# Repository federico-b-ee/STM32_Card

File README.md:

# STM32_Card
This is the first PCB I have designed and professionally assembled. I used KiCAD v7 and JLC PCBs' services.

# Schematic and 3D-view 

# Picture and Demo

*Note: The gif above was made using the Adafruit's Demo:

- [Library](https://github.com/adafruit/Adafruit_IS31FL3731)
- [Overview](https://learn.adafruit.com/i31fl3731-16x9-charliplexed-pwm-led-driver/overview)

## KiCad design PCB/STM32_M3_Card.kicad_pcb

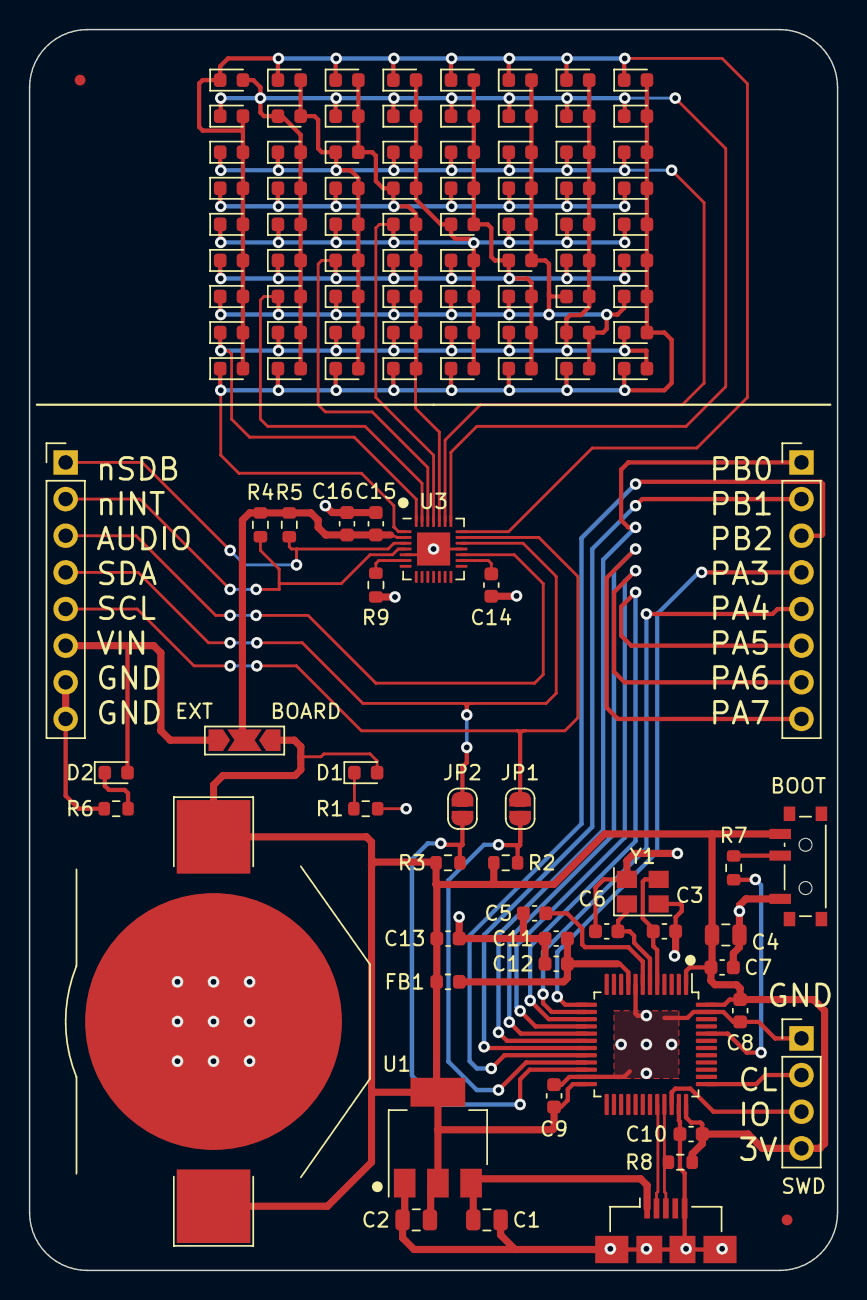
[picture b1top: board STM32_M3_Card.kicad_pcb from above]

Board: 2 copper layers, 56.0 x 86.0 mm, 115 parts (0 on the bottom side), 43 nets.

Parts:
BT1: Coin_Cell; BatteryHolder_Keystone_3002_1x2032
C1, C2: 22u; C_0805_2012Metric
C3, C6: 10p; C_0603_1608Metric
C4: 10u; C_0805_2012Metric
C5, C7, C8, C9, C10, C14, C15: 100n; C_0603_1608Metric
C11: 10n; C_0603_1608Metric
C12, C13, C16: 1u; C_0603_1608Metric
D1, D2, D3, D4, D5, D6, D7, D8, D9, D10, D11, D12, D13, D14, D15, D16, D17, D18, D19, D20, D21, D22, D23, D24, D25, D26, D27, D28, D29, D30, D31, D32, D33, D34, D35, D36, D37, D38, D39, D40, D41, D42, D43, D44, D45, D46, D47, D48, D49, D50, D51, D52, D53, D54, D55, D56, D57, D58, D59, D60, D61, D62, D63, D64, D65, D66, D67, D68, D69, D70, D71, D72, D73, D74: LED (RED); LED_0603_1608Metric
FB1: 120R; L_0603_1608Metric
FID1, FID2: Fiducial; Fiducial_0.75mm_Mask1.5mm
J1, J3: Conn_01x08_Pin; PinHeader_1x08_P2.54mm_Vertical
J2: USB_B_Micro; USB_Micro-B_Amphenol_10104110_Horizontal
J4: Conn_01x04_Pin; PinHeader_1x04_P2.54mm_Vertical
JP1, JP2: SolderJumper_2_Open; SolderJumper-2_P1.3mm_Open_RoundedPad1.0x1.5mm
JP3: SolderJumper_3_Open; SolderJumper-3_P2.0mm_Open_TrianglePad1.0x1.5mm_NumberLabels
R1, R6: 680R; R_0603_1608Metric
R2, R3, R8: 1k5; R_0603_1608Metric
R4, R5, R7, R9: 18k; R_0603_1608Metric
SW1: SW_SPDT; SW_SPDT_PCM12
U1: AMS1117-3.3; SOT-223-3_TabPin2
U2: STM32F103C8T6; LQFP-48_7x7mm_P0.5mm
U3: IS31FL3731-QF; QFN-28-1EP_4x4mm_P0.4mm_EP2.3x2.3mm
Y1: 16MHz 10pF; Crystal_SMD_3225-4Pin_3.2x2.5mm

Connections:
+3.3VA: C11.1, C12.1, FB1.1, U2.9 (VDDA)
+3.3VP: C15.1, C16.1, JP3.2 (C), R4.1, R5.1, U3.2 (VCC)
+3V3: BT1.1 (+), C2.1, C4.1, C7.1, C8.1, C9.1, C10.1, C13.1, D1.2 (A), FB1.2, J4.4, JP3.1 (A), R2.1, R3.1, R8.1, SW1.3 (C), U1.2 (VO), U2.1 (VBAT), U2.24 (VDD), U2.36 (VDD), U2.48 (VDD)
/AMS_LEDK: D1.1 (K), R1.2
/AUD_IS31: J3.3, U3.17 (IN)
/D+: J2.3 (D+), R8.2, U2.33 (PA12)
/D-: J2.2 (D-), U2.32 (PA11)
/EXT_LEDK: D2.1 (K), R6.2
/IS31FL3731/CA1: D3.1 (K), D4.2 (A), D5.2 (A), D6.2 (A), D7.2 (A), D8.2 (A), D9.2 (A), D10.2 (A), D11.2 (A), D12.1 (K), D21.1 (K), D30.1 (K), D39.1 (K), D48.1 (K), D57.1 (K), D66.1 (K), U3.21 (CA1)
/IS31FL3731/CA2: D3.2 (A), D4.1 (K), D13.1 (K), D14.2 (A), D15.2 (A), D16.2 (A), D17.2 (A), D18.2 (A), D19.2 (A), D20.2 (A), D22.1 (K), D31.1 (K), D40.1 (K), D49.1 (K), D58.1 (K), D67.1 (K), U3.22 (CA2)
/IS31FL3731/CA3: D5.1 (K), D12.2 (A), D13.2 (A), D14.1 (K), D23.1 (K), D24.2 (A), D25.2 (A), D26.2 (A), D27.2 (A), D28.2 (A), D29.2 (A), D32.1 (K), D41.1 (K), D50.1 (K), D59.1 (K), D68.1 (K), U3.23 (CA3)
/IS31FL3731/CA4: D6.1 (K), D15.1 (K), D21.2 (A), D22.2 (A), D23.2 (A), D24.1 (K), D33.1 (K), D34.2 (A), D35.2 (A), D36.2 (A), D37.2 (A), D38.2 (A), D42.1 (K), D51.1 (K), D60.1 (K), D69.1 (K), U3.24 (CA4)
/IS31FL3731/CA5: D7.1 (K), D16.1 (K), D25.1 (K), D30.2 (A), D31.2 (A), D32.2 (A), D33.2 (A), D34.1 (K), D43.1 (K), D44.2 (A), D45.2 (A), D46.2 (A), D47.2 (A), D52.1 (K), D61.1 (K), D70.1 (K), U3.25 (CA5)
/IS31FL3731/CA6: D8.1 (K), D17.1 (K), D26.1 (K), D35.1 (K), D39.2 (A), D40.2 (A), D41.2 (A), D42.2 (A), D43.2 (A), D44.1 (K), D53.1 (K), D54.2 (A), D55.2 (A), D56.2 (A), D62.1 (K), D71.1 (K), U3.26 (CA6)
/IS31FL3731/CA7: D9.1 (K), D18.1 (K), D27.1 (K), D36.1 (K), D45.1 (K), D48.2 (A), D49.2 (A), D50.2 (A), D51.2 (A), D52.2 (A), D53.2 (A), D54.1 (K), D63.1 (K), D64.2 (A), D65.2 (A), D72.1 (K), U3.27 (CA7)
/IS31FL3731/CA8: D10.1 (K), D19.1 (K), D28.1 (K), D37.1 (K), D46.1 (K), D55.1 (K), D57.2 (A), D58.2 (A), D59.2 (A), D60.2 (A), D61.2 (A), D62.2 (A), D63.2 (A), D64.1 (K), D73.1 (K), D74.2 (A), U3.28 (CA8)
/IS31FL3731/CA9: D11.1 (K), D20.1 (K), D29.1 (K), D38.1 (K), D47.1 (K), D56.1 (K), D65.1 (K), D66.2 (A), D67.2 (A), D68.2 (A), D69.2 (A), D70.2 (A), D71.2 (A), D72.2 (A), D73.2 (A), D74.1 (K), U3.1 (CA9)
/PA3: J1.4, U2.13 (PA3)
/PA4: J1.5, U2.14 (PA4)
/PA5: J1.6, U2.15 (PA5)
/PA6: J1.7, U2.16 (PA6)
/PA7: J1.8, U2.17 (PA7)
/PB0: J1.1, U2.18 (PB0)
/PB1: J1.2, U2.19 (PB1)
/PB2: J1.3, U2.20 (PB2)
/SCL_IS31: J3.5, JP1.2 (B), U3.20 (SCL)
/SDA_IS31: J3.4, JP2.2 (B), U3.19 (SDA)
/STM32_M3/BOOT0: R7.2, U2.44 (BOOT0)
/STM32_M3/HSE_IN: C3.1, U2.5 (PD0), Y1.3
/STM32_M3/HSE_OUT: C6.1, U2.6 (PD1), Y1.1
/STM32_M3/J_BOOT0: R7.1, SW1.2 (B)
/STM32_M3/NSRST: C5.1, U2.7 (NRST)
/STM32_M3/SCL2: JP1.1 (A), R2.2, U2.21 (PB10)
/STM32_M3/SDA2: JP2.1 (A), R3.2, U2.22 (PB11)
/STM32_M3/SWCLK: J4.2, U2.37 (PA14)
/STM32_M3/SWDIO: J4.3, U2.34 (PA13)
/nINTB_IS31: J3.2, R4.2, U3.4 (~INTB)
/nSDB_IS31: J3.1, R5.2, U3.3 (~SDB)
GND: BT1.2 (-), C1.2, C2.2, C3.2, C4.2, C5.2, C6.2, C7.2, C8.2, C9.2, C10.2, C11.2, C12.2, C13.2, C14.2, C15.2, C16.2, J2.5 (GND), J2.6 (Shield), J3.7, J3.8, J4.1, R1.1, R6.1, R9.2, SW1.1 (A), U1.1 (GND), U2.8 (VSSA), U2.23 (VSS), U2.35 (VSS), U2.47 (VSS), U3.5 (GND), U3.18 (AD), U3.29 (GND), Y1.2, Y1.4
unnamed: C14.1, U3.16 (C_FILT)
unnamed: R9.1, U3.6 (R_EXT)
VBUS: C1.1, J2.1 (VBUS), U1.3 (VI)
VDD: D2.2 (A), J3.6, JP3.3 (B)

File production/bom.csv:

Designator,Footprint,Quantity,Value,LCSC Part #
"C1, C2",0805,2,22u,
"C10, C14, C15, C5, C7, C8, C9",0603,7,100n,
C11,0603,1,10n,
"C12, C13, C16",0603,3,1u,
"C3, C6",0603,2,10p,
C4,0805,1,10u,
"D1, D10, D11, D12, D13, D14, D15, D16, D17, D18, D19, D2, D20, D21, D22, D23, D24, D25, D26, D27, D28, D29, D3, D30, D31, D32, D33, D34, D35, D36, D37, D38, D39, D4, D40, D41, D42, D43, D44, D45, D46, D47, D48, D49, D5, D50, D51, D52, D53, D54, D55, D56, D57, D58, D59, D6, D60, D61, D62, D63, D64, D65, D66, D67, D68, D69, D7, D70, D71, D72, D73, D74, D8, D9",0603,74,LED (RED),
FB1,0603,1,120R,C108298 
J2,USB_Micro-B_Amphenol_10104110_Horizontal,1,USB_B_Micro,C2972784
"JP1, JP2",SolderJumper-2_P1.3mm_Open_RoundedPad1.0x1.5mm,2,SolderJumper_2_Open,
JP4,SolderJumper-3_P2.0mm_Open_TrianglePad1.0x1.5mm_NumberLabels,1,SolderJumper_3_Open,
"R1, R6",0603,2,680R,
"R2, R3, R8",0603,3,1k5,
"R4, R5, R7, R9",0603,4,18k,
SW1,SW_SPDT_PCM12,1,SW_SPDT,C221841
U1,SOT-223-3_TabPin2,1,AMS1117-3.3,C2992570
U2,LQFP-48_7x7mm_P0.5mm,1,STM32F103C8T6,C8734
U3,QFN-28-1EP_4x4mm_P0.4mm_EP2.3x2.3mm,1,IS31FL3731-QF,C191206
Y1,Crystal_SMD_3225-4Pin_3.2x2.5mm,1,16MHz 10pF,C13738
